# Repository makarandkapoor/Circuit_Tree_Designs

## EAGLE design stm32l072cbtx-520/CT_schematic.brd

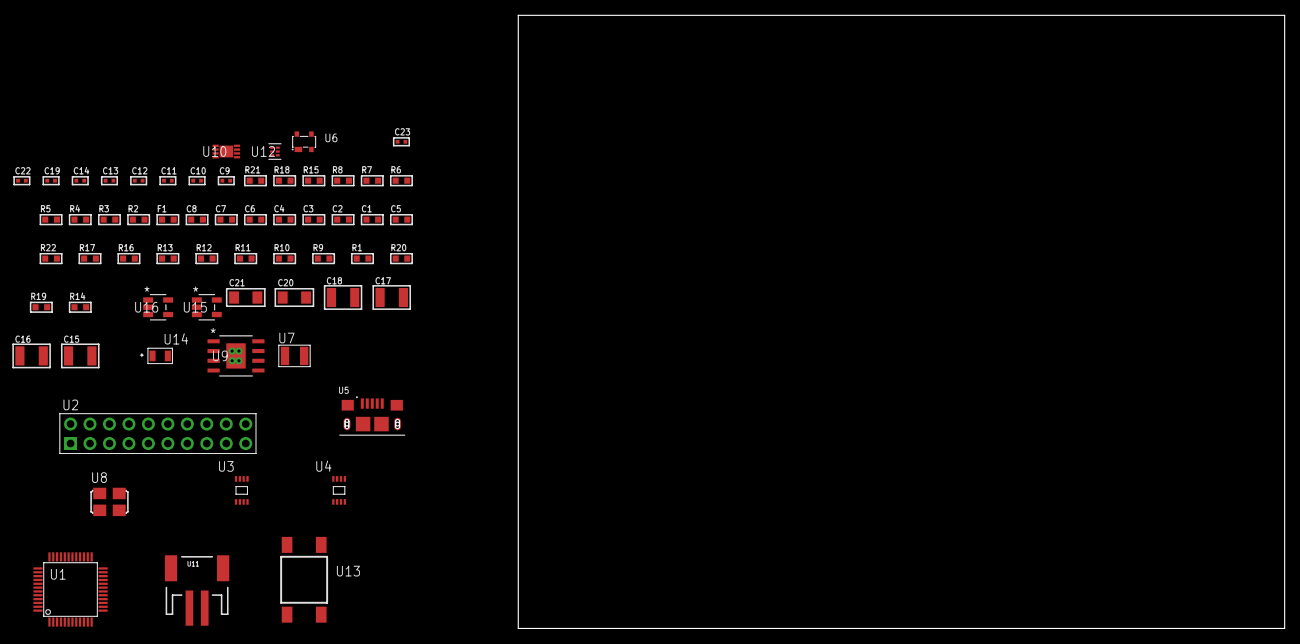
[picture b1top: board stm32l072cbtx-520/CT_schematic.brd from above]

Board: 2 copper layers, 122.6 x 80.0 mm, 62 parts (0 on the bottom side), 31 nets, no tracks yet.

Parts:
C1, C2, C3, C4, C8: 1e-07; C0603
C5: 4.7e-06; C0603
C6: 1e-08; C0603
C7: 1e-06; C0603
C9, C10: 1e-11; C0402
C11, C19: 1e-07; C0402
C12, C13, C14, C22, C23: 1e-08; C0402
C15, C16, C17, C18: 1e-05; C1210
C20, C21: 1e-05; C1206
F1: 240.0; L0603
R1, R9, R10, R11, R12, R13, R16, R17, R22: 10000.0; R0603
R2: 1000.0; R0603
R3: 1600.5; R0603
R4: 4700.0; R0603
R5, R6, R7, R8, R15: 2200.0; R0603
R14: 4031.5447154472; R0603
R18: 9100.0; R0603
R19: 680000.0; R0603
R20: 120000.0; R0603
R21: 2000.0; R0603
U1: STM32L072CBT6; LQFP48
U2: TST-110-05-T-D-RA
U3: 24AA16-I/MC; TDFN-8/6MM
U4: 24AA64T-I/MNY; TDFN-8/6MM
U5: 10118193-0001LF; FCI_10118193-0001LF
U6: prtr5v0u2ax; SOT143B
U7: ABS07-32.768KHZ-7-T
U8: ASFL1-25MHZ-NCS; ASFL1
U9: MIC5234YME; SOIC-8_EP
U10: MCP73831T-2ACI/MC; DFN8_2X3MC
U11: S2B-PH-SM4-TB(LF)(SN); JST-2-SMD
U12: TPS3895ADRYR; SON-6
U13: 4-1437565-2; SW_4-1437565-2
U14: Q65110A2395; LGM67K-G1J2-24-Z
U15, U16: nc7sz125m5x; NC7SZ125M5X

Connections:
CLK_CRYSTAL_U1_3: C9.1, U1.3, U7.1
CLK_CRYSTAL_U1_4: C10.1, U1.4, U7.2
CLK_U1_5: U1.5, U8.3
GND: C1.2, C2.2, C3.2, C4.2, C5.2, C6.2, C7.2, C8.2, C9.2, C10.2, C11.2, C12.2, C13.2, C14.2, C15.2, C16.2, C17.2, C18.2, C19.2, C20.2, C21.2, C22.2, C23.2, R2.2, R9.2, R11.2, R13.2, R15.2, R18.2, R20.2, R21.2, U1.8, U1.23, U1.35, U1.47, U2.4, U2.6, U2.8, U2.10, U2.12, U2.14, U2.16, U2.18, U2.20, U3.4, U3.7, U4.4, U4.7, U5.5, U5.6, U5.7, U5.8, U5.9, U6.1, U8.2, U9.7, U9.EPAD, U10.6, U10.9, U11.2, U12.2, U14.C, U15.2, U15.3, U16.1, U16.3
INPUT_USBPOWER_5V: C20.1, R22.2, U5.1, U6.4, U10.1, U10.2
NET_U1_7: R4.1, U1.7, U16.4
NET_U1_9: C6.1, C7.1, F1.1, U1.9
NET_U1_21: R7.1, U1.21, U3.6
NET_U1_22: R8.1, U1.22, U3.5
NET_U1_30: R5.1, U1.30, U4.6
NET_U1_31: R6.1, U1.31, U4.5
NET_U1_44: R9.1, U1.44
NET_U1_45: R3.1, U1.45, U14.A
NET_U1_46: R1.1, U1.46, U13.3, U13.4
NET_U4_1: R11.1, U4.1
NET_U4_2: R12.1, U4.2
NET_U4_3: R13.1, U4.3
NET_U9_4: R14.2, R15.1, U9.4
NET_U10_5: R22.1, U10.5
NET_U10_8: R21.1, U10.8
NET_U12_1: R17.1, R18.1, U12.1
NET_U12_3: R19.2, R20.1, U12.3
NET_U12_4: R16.1, U12.4, U15.4, U16.2
NET_U13_1: R2.1, U13.1, U13.2
PROC_SYS_SWCLK: U1.37, U2.9
PROC_SYS_SWDIO: U1.34, U2.7
PROC_USB_DM: U1.32, U5.2, U6.3
PROC_USB_DP: U1.33, U5.3, U6.2
RST_OUT_U2_SRESET_B: R10.1, U2.15, U15.1
VCC_S1_3V7: C15.1, C16.1, C21.1, U9.5, U9.8, U10.3, U10.4, U11.1
VCC_TIER1_3V3: C1.1, C2.1, C3.1, C4.1, C5.1, C8.1, C11.1, C12.1, C13.1, C14.1, C17.1, C18.1, C19.1, C22.1, C23.1, F1.2, R1.2, R3.2, R4.2, R5.2, R6.2, R7.2, R8.2, R10.2, R12.2, R14.1, R16.2, R17.2, R19.1, U1.1, U1.24, U1.36, U1.48, U2.1, U3.8, U4.8, U8.4, U9.1, U12.6, U15.5, U16.5

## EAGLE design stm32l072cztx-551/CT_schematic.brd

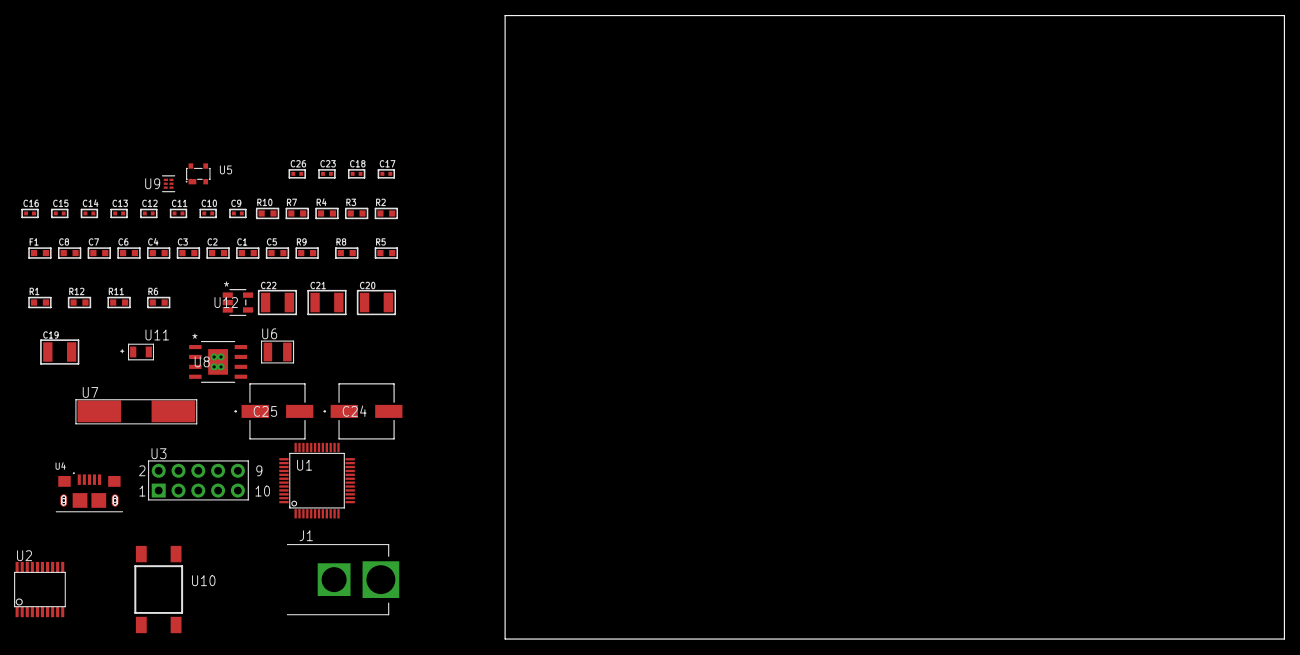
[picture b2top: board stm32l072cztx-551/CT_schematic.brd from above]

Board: 2 copper layers, 156.9 x 80.0 mm, 52 parts (0 on the bottom side), 34 nets, no tracks yet.

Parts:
C1, C2, C3, C4, C8: 1e-07; C0603
C5: 4.7e-06; C0603
C6: 1e-08; C0603
C7: 1e-06; C0603
C9, C10, C11, C12: 1e-11; C0402
C13, C14, C15, C16, C17, C18, C23: 1e-07; C0402
C19, C20, C21, C22: 1e-05; C1210
C24, C25: 0.0001; EXV-9H
C26: 1e-08; C0402
F1: 240.0; L0603
J1: PJ-037B; PJ-037B_PACKAGE
R1, R5, R8, R9: 10000.0; R0603
R2: 1000.0; R0603
R3: 1600.5; R0603
R4: 4700.0; R0603
R6: 4031.5447154472; R0603
R7: 2200.0; R0603
R10: 9100.0; R0603
R11: 680000.0; R0603
R12: 120000.0; R0603
U1: STM32L072CZT6; LQFP48
U2: SP3203ECY-L/TR; TSSOP20-I
U3: HTSS-105-01-G-D
U4: 10118193-0001LF; FCI_10118193-0001LF
U5: prtr5v0u2ax; SOT143B
U6: ABS07-32.768KHZ-7-T
U7: ABLS-25.000MHZ-B2F-T
U8: MIC5234YME; SOIC-8_EP
U9: TPS3895ADRYR; SON-6
U10: 4-1437565-2; SW_4-1437565-2
U11: Q65110A2395; LGM67K-G1J2-24-Z
U12: nc7sz125m5x; NC7SZ125M5X

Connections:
CLK_CRYSTAL_U1_3: C9.1, U1.3, U6.1
CLK_CRYSTAL_U1_4: C10.1, U1.4, U6.2
CLK_CRYSTAL_U1_5: C11.1, U1.5, U7.1
CLK_CRYSTAL_U1_6: C12.1, U1.6, U7.2
GND: C1.2, C2.2, C3.2, C4.2, C5.2, C6.2, C7.2, C8.2, C9.2, C10.2, C11.2, C12.2, C13.2, C14.2, C17.2, C18.2, C19.2, C20.2, C21.2, C22.2, C23.2, C24.2, C25.2, C26.2, J1.2, R2.2, R5.2, R7.2, R10.2, R12.2, U1.8, U1.23, U1.35, U1.47, U2.18, U3.9, U4.5, U4.6, U4.7, U4.8, U4.9, U5.1, U8.7, U8.EPAD, U9.2, U11.C, U12.1, U12.3
NET_U1_7: R4.1, U1.7, U12.4
NET_U1_9: C6.1, C7.1, F1.1, U1.9
NET_U1_44: R5.1, U1.44
NET_U1_45: R3.1, U1.45, U11.A
NET_U1_46: R1.1, U1.46, U10.3, U10.4
NET_U2_1: C15.1, U2.1
NET_U2_2: C17.1, U2.2
NET_U2_3: C15.2, U2.3
NET_U2_4: C16.1, U2.4
NET_U2_5: C16.2, U2.5
NET_U2_6: C18.1, U2.6
NET_U3_3: U2.14, U3.3
NET_U3_4: U2.13, U3.4
NET_U3_5: U2.17, U3.5
NET_U3_6: U2.16, U3.6
NET_U5_4: U4.1, U5.4
NET_U8_4: R6.2, R7.1, U8.4
NET_U9_1: R9.1, R10.1, U9.1
NET_U9_3: R11.2, R12.1, U9.3
NET_U9_4: R8.1, U9.4, U12.2
NET_U10_1: R2.1, U10.1, U10.2
PROC_LPUART1_CTS: U1.16, U2.8
PROC_LPUART1_RTS: U1.19, U2.10
PROC_LPUART1_RX: U1.13, U2.11
PROC_LPUART1_TX: U1.12, U2.7
PROC_USB_DM: U1.32, U4.2, U5.3
PROC_USB_DP: U1.33, U4.3, U5.2
VCC_S1_10V3: C19.1, C20.1, C24.1, C25.1, J1.1, U8.5, U8.8
VCC_TIER1_3V3: C1.1, C2.1, C3.1, C4.1, C5.1, C8.1, C13.1, C14.1, C21.1, C22.1, C23.1, C26.1, F1.2, R1.2, R3.2, R4.2, R6.1, R8.2, R9.2, R11.1, U1.1, U1.24, U1.36, U1.48, U2.12, U2.19, U8.1, U9.6, U12.5

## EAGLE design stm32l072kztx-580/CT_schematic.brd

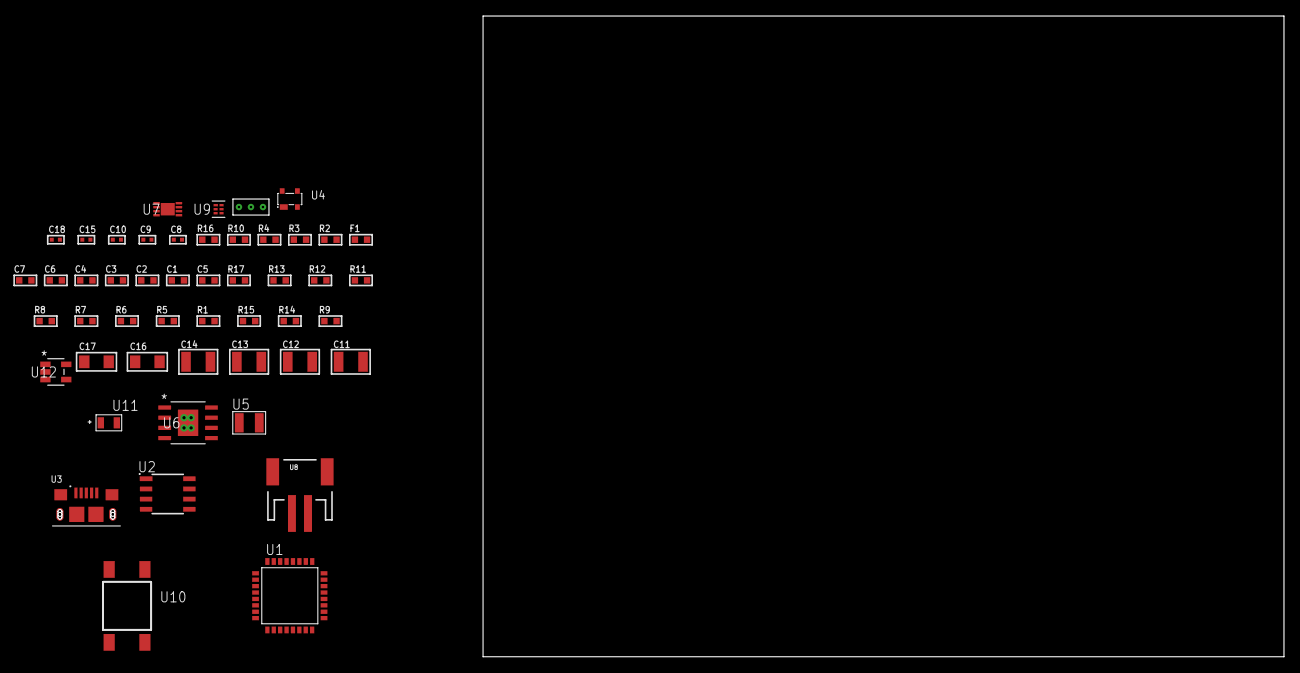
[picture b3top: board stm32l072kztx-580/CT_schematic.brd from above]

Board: 2 copper layers, 153.1 x 80.0 mm, 49 parts (0 on the bottom side), 28 nets, no tracks yet.

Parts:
C1, C2, C3, C4: 1e-07; C0603
C5: 4.7e-06; C0603
C6: 1e-08; C0603
C7: 1e-06; C0603
C8, C9: 1e-11; C0402
C10, C18: 1e-08; C0402
C11, C12, C13, C14: 1e-05; C1210
C15: 1e-07; C0402
C16, C17: 1e-05; C1206
F1: 240.0; L0603
R1, R5, R6, R7, R8, R11, R12, R17: 10000.0; R0603
R2: 1000.0; R0603
R3: 910.0; R0603
R4: 4700.0; R0603
R9: 1402.2764227642; R0603
R10: 2200.0; R0603
R13: 82000.0; R0603
R14: 300000.0; R0603
R15: 120000.0; R0603
R16: 2000.0; R0603
U1: STM32L072KZT6; LQFP32
U2: AT25256B-SSHL-T; SOIC-8
U3: 10118193-0001LF; FCI_10118193-0001LF
U4: prtr5v0u2ax; SOT143B
U5: ABS07-32.768KHZ-7-T
U6: MIC5234YME; SOIC-8_EP
U7: MCP73831T-2ACI/MC; DFN8_2X3MC
U8: S2B-PH-SM4-TB(LF)(SN); JST-2-SMD
U9: TPS3895ADRYR; SON-6
U10: 4-1437565-2; SW_4-1437565-2
U11: Q65110A2395; LGM67K-G1J2-24-Z
U12: nc7sz125m5x; NC7SZ125M5X
U13: Dummy; DUMMY_PACKAGE_101

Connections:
CLK_CRYSTAL_U1_2: C8.1, U1.2, U5.1
CLK_CRYSTAL_U1_3: C9.1, U1.3, U5.2
GND: C1.2, C2.2, C3.2, C4.2, C5.2, C6.2, C7.2, C8.2, C9.2, C10.2, C11.2, C12.2, C13.2, C14.2, C15.2, C16.2, C17.2, C18.2, R2.2, R5.2, R10.2, R13.2, R15.2, R16.2, U1.16, U1.32, U2.4, U3.5, U3.6, U3.7, U3.8, U3.9, U4.1, U6.7, U6.EPAD, U7.6, U7.9, U8.2, U9.2, U11.C, U12.1, U12.3, U13.1
INPUT_USBPOWER_5V: C16.1, R17.2, U3.1, U4.4, U7.1, U7.2
NET_U1_4: R4.1, U1.4, U12.4
NET_U1_5: C6.1, C7.1, F1.1, U1.5
NET_U1_29: R3.1, U1.29, U11.A
NET_U1_30: R1.1, U1.30, U10.3, U10.4
NET_U1_31: R5.1, U1.31
NET_U2_3: R6.1, U2.3
NET_U2_7: R8.1, U2.7
NET_U6_4: R9.2, R10.1, U6.4
NET_U7_5: R17.1, U7.5
NET_U7_8: R16.1, U7.8
NET_U9_1: R12.1, R13.1, U9.1
NET_U9_3: R14.2, R15.1, U9.3
NET_U9_4: R11.1, U9.4, U12.2
NET_U10_1: R2.1, U10.1, U10.2
PROC_PA0: U1.6, U13.2
PROC_PA1: U1.7, U13.3
PROC_SPI1_MISO: U1.12, U2.2
PROC_SPI1_MOSI: U1.13, U2.5
PROC_SPI1_NSS: R7.1, U1.10, U2.1
PROC_SPI1_SCK: U1.11, U2.6
PROC_USB_DM: U1.21, U3.2, U4.3
PROC_USB_DP: U1.22, U3.3, U4.2
VCC_S1_3V7: C11.1, C12.1, C17.1, U6.5, U6.8, U7.3, U7.4, U8.1
VCC_TIER1_1V8: C1.1, C2.1, C3.1, C4.1, C5.1, C10.1, C13.1, C14.1, C15.1, C18.1, F1.2, R1.2, R3.2, R4.2, R6.2, R7.2, R8.2, R9.1, R11.2, R12.2, R14.1, U1.1, U1.17, U2.8, U6.1, U9.6, U12.5

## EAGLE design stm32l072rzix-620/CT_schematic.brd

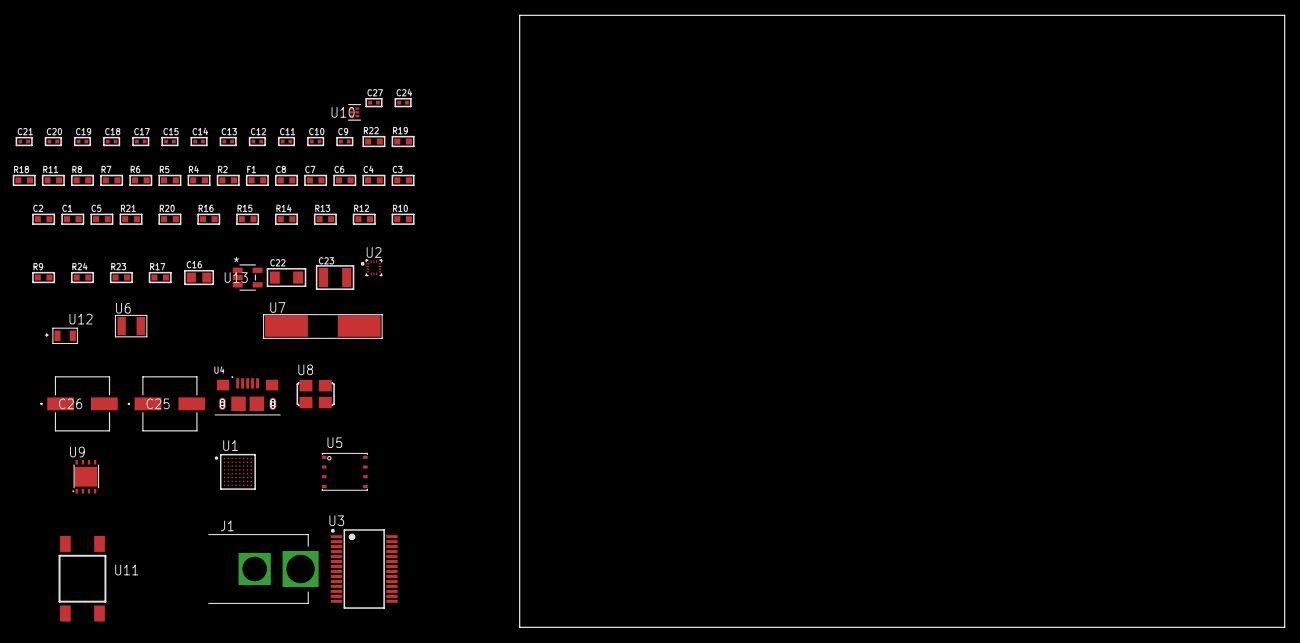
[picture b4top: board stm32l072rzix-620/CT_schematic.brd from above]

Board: 2 copper layers, 64 parts (0 on the bottom side), 36 nets, no tracks yet.

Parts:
C1, C2, C3, C4, C8: 1e-07; C0603
C5: 4.7e-06; C0603
C6: 1e-08; C0603
C7: 1e-06; C0603
C9, C10, C11, C12: 1e-11; C0402
C13, C14, C15, C17, C18, C24: 1e-07; C0402
C16: 4.7e-06; C0805
C19, C20, C21, C27: 1e-08; C0402
C22: 1e-05; C1206
C23: 1e-05; C1210
C25, C26: 0.0001; EXV-9H
F1: 240.0; L0603
J1: PJ-037B; PJ-037B_PACKAGE
R2, R19: 1000.0; R0603
R4, R11: 4700.0; R0603
R5, R6, R7, R8: 2200.0; R0603
R9, R10, R12, R13, R14, R15, R16, R20, R21: 10000.0; R0603
R17: 100000.0; R0603
R18: 2231.0; R0603
R22: 9100.0; R0603
R23: 680000.0; R0603
R24: 120000.0; R0603
U1: STM32L072RZI6; UFBGA64
U2: BMC150; LGA14R35P5X6_200X200X100
U3: FT232RL-REEL; SSOP-28
U4: 10118193-0001LF; FCI_10118193-0001LF
U5: 24AA256-I/MF; DFN8-S
U6: ABS07-32.768KHZ-7-T
U7: ABLS-25.000MHZ-B2F-T
U8: ASFL1-12MHZ-NCS; ASFL1
U9: LP3878SDX-ADJ/NOPB; WSON-8
U10: TPS3895ADRYR; SON-6
U11: 4-1437565-2; SW_4-1437565-2
U12: Q65110A2395; LGM67K-G1J2-24-Z
U13: nc7sz125m5x; NC7SZ125M5X

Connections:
CLK_CRYSTAL_U1_A1: C9.1, U1.A1, U6.1
CLK_CRYSTAL_U1_B1: C10.1, U1.B1, U6.2
CLK_CRYSTAL_U1_C1: C11.1, U1.C1, U7.1
CLK_CRYSTAL_U1_D1: C12.1, U1.D1, U7.2
CLK_U3_27: U3.27, U8.3
GND: C1.2, C2.2, C3.2, C4.2, C5.2, C6.2, C7.2, C8.2, C9.2, C10.2, C11.2, C12.2, C13.2, C14.2, C15.2, C16.2, C17.2, C18.2, C19.2, C20.2, C21.2, C22.2, C23.2, C24.2, C25.2, C26.2, C27.2, J1.2, R2.2, R9.2, R13.2, R14.2, R16.2, R19.2, R22.2, R24.2, U1.C2, U1.D4, U1.D5, U1.D6, U1.F1, U2.1, U2.6, U2.7, U2.9, U3.7, U3.18, U3.21, U3.25, U3.26, U4.5, U4.6, U4.7, U4.8, U4.9, U5.4, U8.2, U9.3, U9.PAD, U10.2, U12.C, U13.1, U13.3
NET_U1_A3: R6.1, U1.A3, U2.14
NET_U1_B3: R5.1, U1.B3, U2.11
NET_U1_B4: R9.1, U1.B4
NET_U1_E1: R4.1, U1.E1, U13.4
NET_U1_F8: R8.1, U1.F8, U5.5
NET_U1_G7: R7.1, U1.G7, U5.6
NET_U1_H1: C6.1, C7.1, F1.1, U1.G1, U1.H1
NET_U1_H8: U11.3, U11.4
NET_U3_14: R12.1, U3.14
NET_U3_17: C17.1, U3.17
NET_U3_19: R13.1, U3.19
NET_U4_1: R11.1, U4.1
NET_U4_2: U3.16, U4.2
NET_U4_3: U3.15, U4.3
NET_U5_1: R14.1, U5.1
NET_U5_2: R15.1, U5.2
NET_U5_3: R16.1, U5.3
NET_U9_1: C21.1, U9.1
NET_U9_6: R18.2, R19.1, U9.6
NET_U9_8: R17.1, U9.8
NET_U10_1: R21.1, R22.1, U10.1
NET_U10_3: R23.2, R24.1, U10.3
NET_U10_4: R20.1, U10.4, U13.2
NET_U11_1: R2.1, U11.1, U11.2
PROC_LPUART1_CTS: U1.G4, U3.3
PROC_LPUART1_RTS: U1.B5, U3.11
PROC_LPUART1_RX: U1.A8, U3.1
PROC_LPUART1_TX: U1.A7, U3.5
VCC_S1_11V0: C22.1, C25.1, C26.1, J1.1, R17.2, U9.4
VCC_TIER1_3V3: C1.1, C2.1, C3.1, C4.1, C5.1, C8.1, C13.1, C14.1, C15.1, C16.1, C18.1, C19.1, C20.1, C23.1, C24.1, C27.1, F1.2, R4.2, R5.2, R6.2, R7.2, R8.2, R10.1, R10.2, R12.2, R15.2, R18.1, R20.2, R21.2, R23.1, U1.B2, U1.D2, U1.E4, U1.E5, U1.E6, U2.8, U2.10, U2.12, U2.13, U3.4, U3.20, U5.7, U5.8, U8.4, U9.5, U10.6, U13.5

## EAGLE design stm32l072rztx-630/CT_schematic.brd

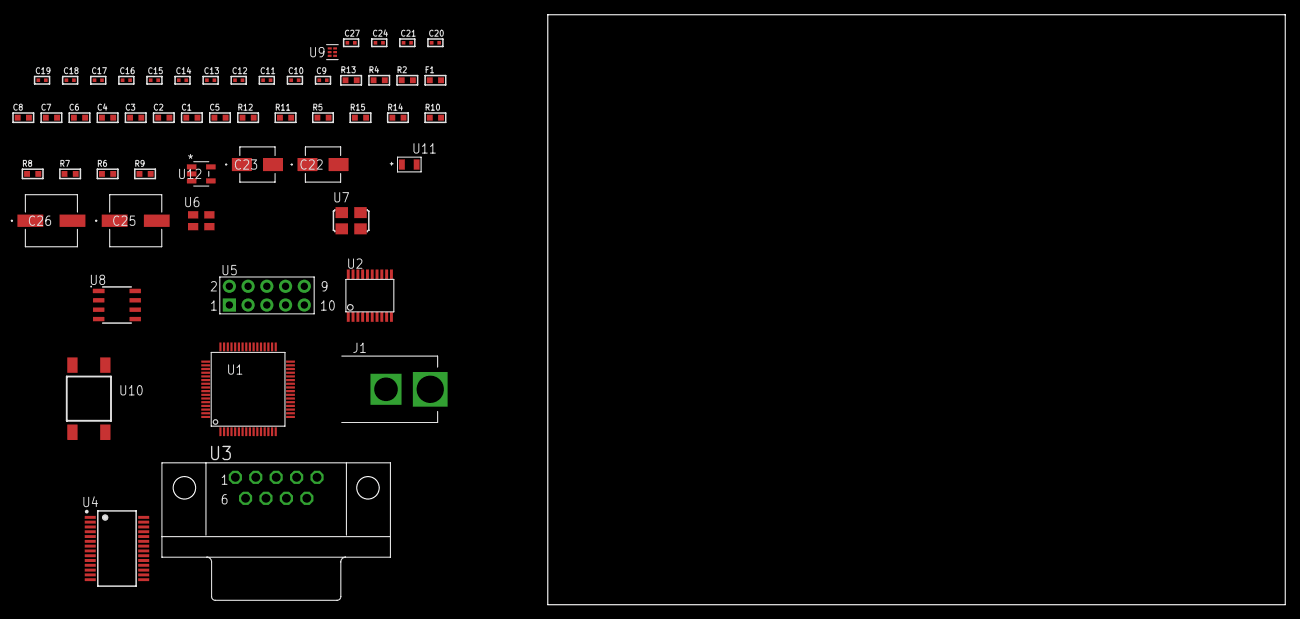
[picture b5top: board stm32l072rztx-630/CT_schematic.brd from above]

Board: 2 copper layers, 100.0 x 80.0 mm, 54 parts (0 on the bottom side), 45 nets, no tracks yet.

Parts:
C1, C2, C3, C4, C8: 1e-07; C0603
C5: 4.7e-06; C0603
C6: 1e-08; C0603
C7: 1e-06; C0603
C9, C10, C11, C12, C13, C14, C15, C16, C17, C18, C19, C24: 1e-07; C0402
C20, C21, C27: 1e-08; C0402
C22: 1e-06; EXV-9B
C23: 2.2e-06; EXV-9B
C25, C26: 0.0001; EXV-9H
F1: 240.0; L0603
J1: PJ-037B; PJ-037B_PACKAGE
R2: 1000.0; R0603
R4: 4700.0; R0603
R5, R11, R12: 10000.0; R0603
R6, R7, R8, R10: 100000.0; R0603
R9: 164658.62; R0603
R13: 9100.0; R0603
R14: 680000.0; R0603
R15: 120000.0; R0603
U1: STM32L072RZT6; LQFP64
U2: SP3203ECY-L/TR; TSSOP20-I
U3: 182-009-113R531; 182-009-MALE
U4: ST3241EBPR; SSOP-28
U5: HTSS-105-01-G-D
U6: ASEK-32.768KHz-ECST; ASEK
U7: ASFL1-25MHZ-NCS; ASFL1
U8: LP2954AIMX/NOPB; LP2954
U9: TPS3895ADRYR; SON-6
U10: 4-1437565-2; SW_4-1437565-2
U11: Q65110A2395; LGM67K-G1J2-24-Z
U12: nc7sz125m5x; NC7SZ125M5X

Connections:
CLK_U1_3: U1.3, U6.3
CLK_U1_5: U1.5, U7.3
GND: C1.2, C2.2, C3.2, C4.2, C5.2, C6.2, C7.2, C8.2, C9.2, C10.2, C13.2, C14.2, C15.2, C18.2, C19.2, C20.2, C21.2, C22.2, C23.2, C24.2, C25.2, C26.2, C27.2, J1.2, R2.2, R5.2, R10.2, R13.2, R15.2, U1.12, U1.18, U1.31, U1.47, U1.63, U2.18, U3.5, U4.23, U4.25, U5.9, U6.2, U7.2, U8.4, U9.2, U11.C, U12.1, U12.3
NET_U1_7: R4.1, U1.7, U12.4
NET_U1_13: C6.1, C7.1, F1.1, U1.13
NET_U1_60: R5.1, U1.60
NET_U1_62: U10.3, U10.4
NET_U2_1: C11.1, U2.1
NET_U2_2: C13.1, U2.2
NET_U2_3: C11.2, U2.3
NET_U2_4: C12.1, U2.4
NET_U2_5: C12.2, U2.5
NET_U2_6: C14.1, U2.6
NET_U3_2: U2.14, U3.2
NET_U3_3: U2.17, U3.3
NET_U3_7: U2.13, U3.7
NET_U3_8: U2.16, U3.8
NET_U4_1: C17.1, U4.1
NET_U4_2: C17.2, U4.2
NET_U4_3: C19.1, U4.3
NET_U4_22: R6.1, U4.22
NET_U4_24: C16.2, U4.24
NET_U4_27: C18.1, U4.27
NET_U4_28: C16.1, U4.28
NET_U5_3: U4.4, U5.3
NET_U5_4: U4.5, U5.4
NET_U5_5: U4.9, U5.5
NET_U5_6: U4.10, U5.6
NET_U8_3: R8.1, U8.3
NET_U8_5: R7.1, U8.5
NET_U8_7: R9.2, R10.1, U8.7
NET_U9_1: R12.1, R13.1, U9.1
NET_U9_3: R14.2, R15.1, U9.3
NET_U9_4: R11.1, U9.4, U12.2
NET_U10_1: R2.1, U10.1, U10.2
PROC_LPUART1_CTS: U1.22, U2.8
PROC_LPUART1_RTS: U1.27, U2.10
PROC_LPUART1_RX: U1.8, U2.11
PROC_LPUART1_TX: U1.9, U2.7
PROC_USART1_CTS: U1.44, U4.13
PROC_USART1_RTS: U1.45, U4.18
PROC_USART1_RX: U1.43, U4.19
PROC_USART1_TX: U1.42, U4.14
VCC_S1_6V2: C22.1, C25.1, C26.1, J1.1, R8.2, U8.8
VCC_TIER1_3V3: C1.1, C2.1, C3.1, C4.1, C5.1, C8.1, C9.1, C10.1, C15.1, C20.1, C21.1, C23.1, C24.1, C27.1, F1.2, R4.2, R6.2, R7.2, R9.1, R11.2, R12.2, R14.1, U1.1, U1.19, U1.32, U1.48, U1.64, U2.12, U2.19, U4.26, U6.4, U7.4, U8.1, U9.6, U12.5

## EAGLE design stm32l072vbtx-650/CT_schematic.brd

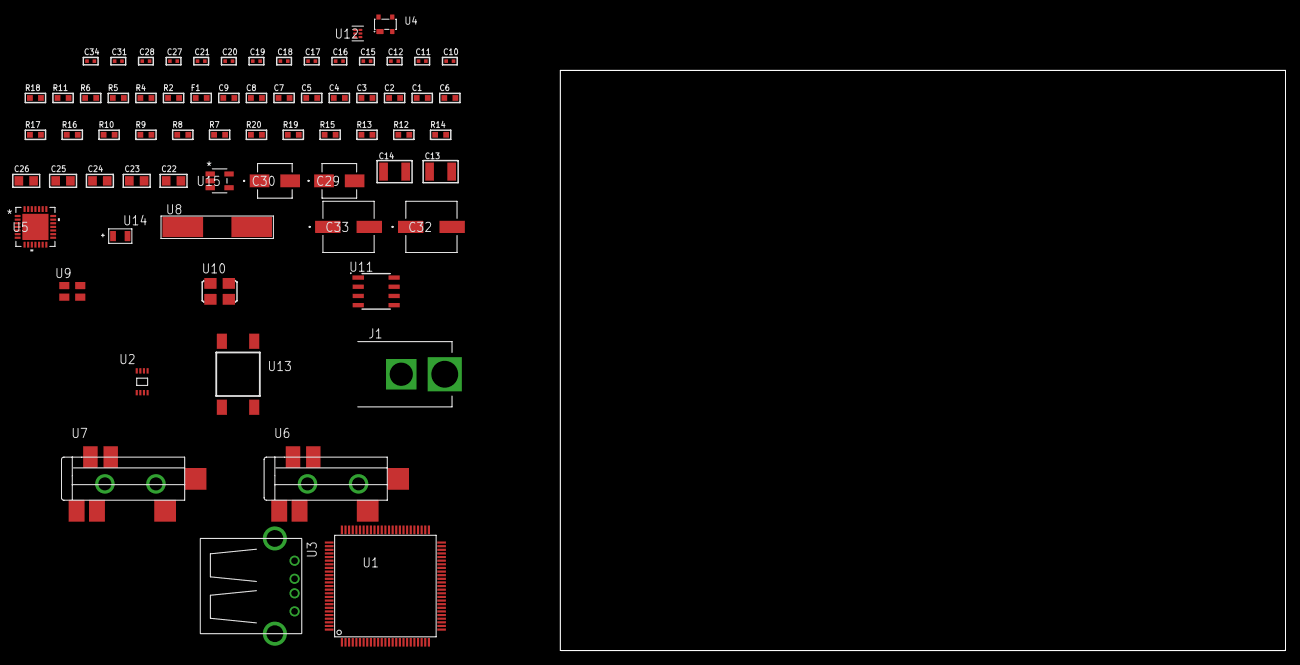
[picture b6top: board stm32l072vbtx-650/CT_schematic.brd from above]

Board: 2 copper layers, 100.0 x 80.0 mm, 69 parts (0 on the bottom side), 30 nets, no tracks yet.

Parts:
C1, C2, C3, C4, C5, C9: 1e-07; C0603
C6: 4.7e-06; C0603
C7: 1e-08; C0603
C8: 1e-06; C0603
C10, C11: 1e-11; C0402
C12, C27, C28, C34: 1e-08; C0402
C13, C14: 2.2e-05; C1210
C15, C16: 1e-09; C0402
C17, C18, C19, C20, C21, C31: 1e-07; C0402
C22, C23, C24, C25, C26: 1e-05; C0805
C29: 1e-06; EXV-9B
C30: 2.2e-06; EXV-9B
C32, C33: 0.0001; EXV-9H
F1: 240.0; L0603
J1: PJ-037B; PJ-037B_PACKAGE
R2: 1000.0; R0603
R4: 4700.0; R0603
R5, R6: 2200.0; R0603
R7, R16, R17: 10000.0; R0603
R8, R9, R10: 47000.0; R0603
R11: 680.0; R0603
R12, R13, R15: 100000.0; R0603
R14: 164658.62; R0603
R18: 9100.0; R0603
R19: 680000.0; R0603
R20: 120000.0; R0603
U1: STM32L072VBT6; LQFP100
U2: 24AA16-I/MC; TDFN-8/6MM
U3: 61400416021; USB-A-H
U4: prtr5v0u2ax; SOT143B
U5: WM8731CLSEFL; QFN-28
U6, U7: SJ-43515TS-SMT-TR
U8: ABLS-25.000MHZ-B2F-T
U9: ASEK-32.768KHz-ECST; ASEK
U10: ASFL1-12.288MHZ-EC-T; ASFL1
U11: LP2954AIMX/NOPB; LP2954
U12: TPS3895ADRYR; SON-6
U13: 4-1437565-2; SW_4-1437565-2
U14: Q65110A2395; LGM67K-G1J2-24-Z
U15: nc7sz125m5x; NC7SZ125M5X

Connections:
CLK_CRYSTAL_U1_12: C10.1, U1.12, U8.1
CLK_CRYSTAL_U1_13: C11.1, U1.13, U8.2
CLK_U1_8: U1.8, U9.3
CLK_U5_1: U5.1, U10.3
GND: C1.2, C2.2, C3.2, C4.2, C5.2, C6.2, C7.2, C8.2, C9.2, C10.2, C11.2, C12.2, C16.2, C17.2, C18.2, C19.2, C20.2, C21.2, C22.2, C23.2, C24.2, C25.2, C26.2, C27.2, C28.2, C29.2, C30.2, C31.2, C32.2, C33.2, C34.2, J1.2, R2.2, R7.2, R8.2, R9.2, R10.2, R15.2, R18.2, R20.2, U1.19, U1.20, U1.27, U1.49, U1.74, U1.99, U2.4, U3.4, U3.5, U3.6, U4.1, U5.4, U5.15, U5.19, U5.25, U5.26, U5.29, U6.1, U7.1, U9.2, U10.2, U11.4, U12.2, U14.C, U15.1, U15.3
NET_U1_14: R4.1, U1.14, U15.4
NET_U1_22: C7.1, C8.1, F1.1, U1.21, U1.22
NET_U1_68: R5.1, U1.68, U2.6
NET_U1_69: R6.1, U1.69, U2.5
NET_U1_94: R7.1, U1.94
NET_U1_98: U13.3, U13.4
NET_U4_4: U3.1, U4.4
NET_U5_20: C21.1, C26.1, U5.20
NET_U6_2: C14.1, R9.1, U6.2
NET_U6_5: C13.1, R8.1, U6.5
NET_U7_5: C15.1, C16.1, R10.1, R11.1, U7.5
NET_U11_3: R13.1, U11.3
NET_U11_5: R12.1, U11.5
NET_U11_7: R14.2, R15.1, U11.7
NET_U12_1: R17.1, R18.1, U12.1
NET_U12_3: R19.2, R20.1, U12.3
NET_U12_4: R16.1, U12.4, U15.2
NET_U13_1: R2.1, U13.1, U13.2
PROC_I2S2_CK: U1.52, U5.7
PROC_I2S2_SD: U1.18, U5.8
PROC_I2S2_WS: U1.51, U5.9, U5.11
PROC_USB_DM: U1.70, U3.2, U4.3
PROC_USB_DP: U1.71, U3.3, U4.2
VCC_S1_11V5: C29.1, C32.1, C33.1, J1.1, R13.2, U11.8
VCC_TIER1_3V3: C1.1, C2.1, C3.1, C4.1, C5.1, C6.1, C9.1, C12.1, C17.1, C18.1, C19.1, C20.1, C22.1, C23.1, C24.1, C25.1, C27.1, C28.1, C30.1, C31.1, C34.1, F1.2, R4.2, R5.2, R6.2, R12.2, R14.1, R16.2, R17.2, R19.1, U1.6, U1.28, U1.50, U1.73, U1.75, U1.100, U2.7, U2.8, U5.3, U5.5, U5.12, U5.18, U9.4, U10.4, U11.1, U12.6, U15.5

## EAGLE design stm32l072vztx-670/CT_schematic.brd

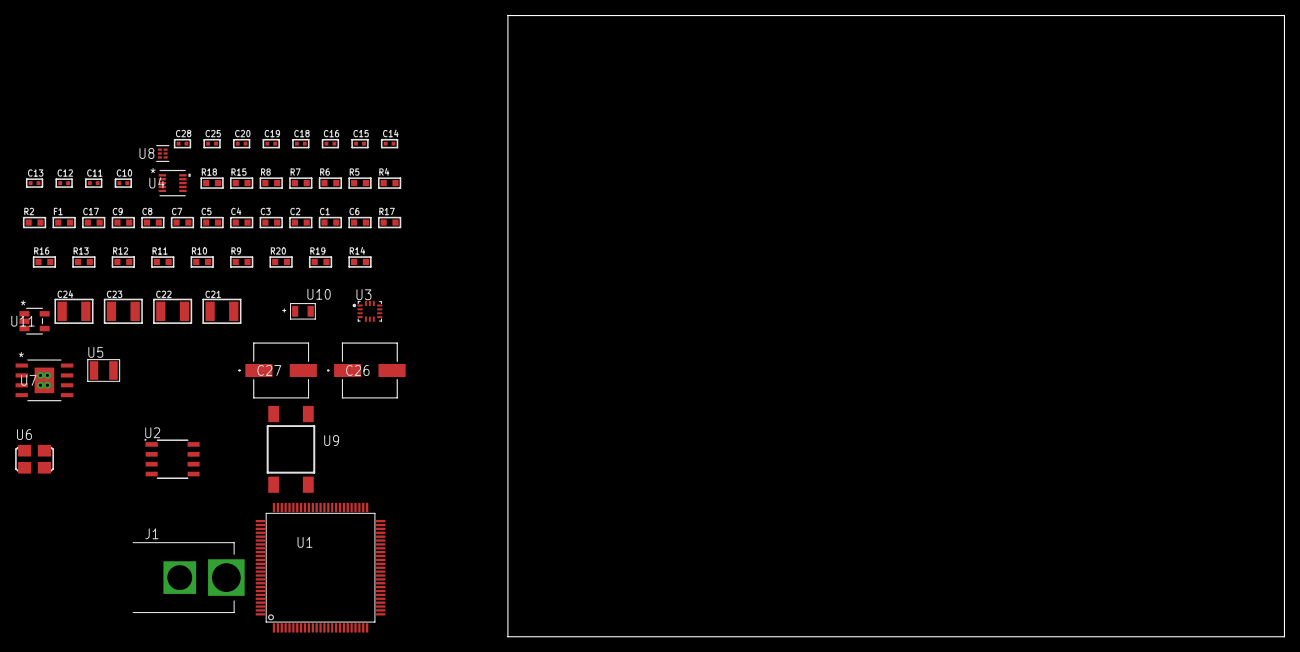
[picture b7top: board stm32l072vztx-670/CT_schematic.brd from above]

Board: 2 copper layers, 100.0 x 80.0 mm, 59 parts (0 on the bottom side), 26 nets, no tracks yet.

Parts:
C1, C2, C3, C4, C5, C9: 1e-07; C0603
C6: 4.7e-06; C0603
C7: 1e-08; C0603
C8, C17: 1e-06; C0603
C10, C11: 1e-11; C0402
C12, C20, C28: 1e-08; C0402
C13, C14, C15, C16, C18, C19, C25: 1e-07; C0402
C21, C22, C23, C24: 1e-05; C1210
C26, C27: 0.0001; EXV-9H
F1: 240.0; L0603
J1: PJ-037B; PJ-037B_PACKAGE
R2: 1000.0; R0603
R4: 4700.0; R0603
R5, R6, R7, R8, R15: 2200.0; R0603
R9, R10, R11, R12, R13, R16, R17: 10000.0; R0603
R14: 4031.5447154472; R0603
R18: 9100.0; R0603
R19: 680000.0; R0603
R20: 120000.0; R0603
U1: STM32L072VZT6; LQFP100
U2: AT25M02-SSHD-T; SOIC-8
U3: BMG250; LGA-14
U4: MAG3110FCR1; DFN-10
U5: ABS07-32.768KHZ-7-T
U6: ASFL1-25MHZ-NCS; ASFL1
U7: MIC5234YME; SOIC-8_EP
U8: TPS3895ADRYR; SON-6
U9: 4-1437565-2; SW_4-1437565-2
U10: Q65110A2395; LGM67K-G1J2-24-Z
U11: nc7sz125m5x; NC7SZ125M5X

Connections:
CLK_CRYSTAL_U1_8: C10.1, U1.8, U5.1
CLK_CRYSTAL_U1_9: C11.1, U1.9, U5.2
CLK_U1_12: U1.12, U6.3
GND: C1.2, C2.2, C3.2, C4.2, C5.2, C6.2, C7.2, C8.2, C9.2, C10.2, C11.2, C12.2, C13.2, C14.2, C15.2, C16.2, C17.2, C18.2, C19.2, C20.2, C21.2, C22.2, C23.2, C24.2, C25.2, C26.2, C27.2, C28.2, J1.2, R2.2, R9.2, R15.2, R18.2, R20.2, U1.19, U1.20, U1.27, U1.49, U1.74, U1.99, U2.4, U3.1, U3.6, U3.7, U4.5, U4.10, U6.2, U7.7, U7.EPAD, U8.2, U10.C, U11.1, U11.3
NET_U1_14: R4.1, U1.14, U11.4
NET_U1_22: C7.1, C8.1, F1.1, U1.21, U1.22
NET_U1_47: R7.1, U1.47, U3.13
NET_U1_48: R8.1, U1.48, U3.14
NET_U1_68: R5.1, U1.68, U4.7
NET_U1_69: R6.1, U1.69, U4.6
NET_U1_94: R9.1, U1.94
NET_U1_98: U9.3, U9.4
NET_U2_3: R10.1, U2.3
NET_U2_7: R12.1, U2.7
NET_U3_12: R13.1, U3.12
NET_U4_1: C15.1, U4.1
NET_U4_4: C18.1, U4.4
NET_U7_4: R14.2, R15.1, U7.4
NET_U8_1: R17.1, R18.1, U8.1
NET_U8_3: R19.2, R20.1, U8.3
NET_U8_4: R16.1, U8.4, U11.2
NET_U9_1: R2.1, U9.1, U9.2
PROC_GPIO_TO_U3_INT1: U1.1, U3.4
PROC_SPI1_NSS: R11.1, U2.1
VCC_S1_7V3: C21.1, C22.1, C26.1, C27.1, J1.1, U7.5, U7.8
VCC_TIER1_3V3: C1.1, C2.1, C3.1, C4.1, C5.1, C6.1, C9.1, C12.1, C13.1, C14.1, C16.1, C17.1, C19.1, C20.1, C23.1, C24.1, C25.1, C28.1, F1.2, R4.2, R5.2, R6.2, R7.2, R8.2, R10.2, R11.2, R12.2, R13.2, R14.1, R16.2, R17.2, R19.1, U1.6, U1.28, U1.50, U1.73, U1.75, U1.100, U2.8, U3.5, U3.8, U4.2, U4.8, U6.4, U7.1, U8.6, U11.5

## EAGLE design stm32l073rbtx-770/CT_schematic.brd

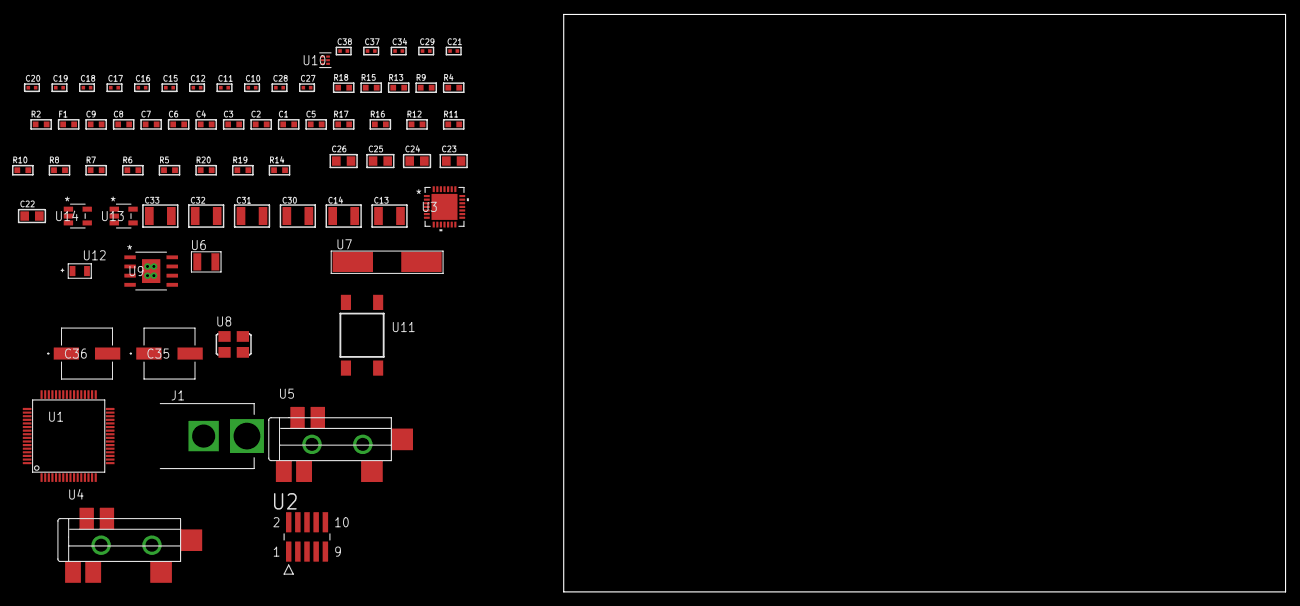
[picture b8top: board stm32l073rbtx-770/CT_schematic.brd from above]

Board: 2 copper layers, 100.0 x 80.0 mm, 72 parts (0 on the bottom side), 29 nets, no tracks yet.

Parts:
C1, C2, C3, C4, C6, C9: 1e-07; C0603
C5: 4.7e-06; C0603
C7: 1e-08; C0603
C8: 1e-06; C0603
C10, C11: 1e-11; C0402
C12, C17, C18, C19, C20, C21, C34: 1e-07; C0402
C13, C14: 2.2e-05; C1210
C15, C16: 1e-09; C0402
C22, C23, C24, C25, C26: 1e-05; C0805
C27, C28: 2.2e-11; C0402
C29, C37, C38: 1e-08; C0402
C30, C31, C32, C33: 1e-05; C1210
C35, C36: 0.0001; EXV-9H
F1: 240.0; L0603
J1: PJ-037B; PJ-037B_PACKAGE
R2: 1000.0; R0603
R4: 4700.0; R0603
R5, R6, R7, R8, R16, R17: 10000.0; R0603
R9: 5.0; R0603
R10, R11, R12: 47000.0; R0603
R13: 680.0; R0603
R14: 4031.5447154472; R0603
R15: 2200.0; R0603
R18: 9100.0; R0603
R19: 680000.0; R0603
R20: 120000.0; R0603
U1: STM32L073RBT6; LQFP64
U2: FTSH-105-01-L-DV-K; SAMTEC_FTSH-105-01-L-DV-K
U3: WM8731CLSEFL; QFN-28
U4, U5: SJ-43515TS-SMT-TR
U6: ABS07-32.768KHZ-7-T
U7: ABLS-12.288MHZ-B4-T
U8: ASFL1-25MHZ-NCS; ASFL1
U9: MIC5234YME; SOIC-8_EP
U10: TPS3895ADRYR; SON-6
U11: 4-1437565-2; SW_4-1437565-2
U12: Q65110A2395; LGM67K-G1J2-24-Z
U13, U14: nc7sz125m5x; NC7SZ125M5X

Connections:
CLK_CRYSTAL_U1_3: C10.1, U1.3, U6.1
CLK_CRYSTAL_U1_4: C11.1, U1.4, U6.2
CLK_CRYSTAL_U3_1: C27.1, U3.1, U7.1
CLK_CRYSTAL_U3_2: C28.1, U3.2, U7.2
CLK_U1_5: U1.5, U8.3
GND: C1.2, C2.2, C3.2, C4.2, C5.2, C6.2, C7.2, C8.2, C9.2, C10.2, C11.2, C12.2, C16.2, C17.2, C18.2, C19.2, C20.2, C21.2, C22.2, C23.2, C24.2, C25.2, C26.2, C27.2, C28.2, C29.2, C30.2, C31.2, C32.2, C33.2, C34.2, C35.2, C36.2, C37.2, C38.2, J1.2, R2.2, R5.2, R9.2, R10.2, R11.2, R12.2, R15.2, R18.2, R20.2, U1.12, U1.18, U1.31, U1.47, U1.63, U2.3, U2.5, U3.4, U3.15, U3.19, U3.25, U3.26, U3.29, U4.1, U5.1, U8.2, U9.7, U9.EPAD, U10.2, U12.C, U13.2, U13.3, U14.1, U14.3
NET_U1_1: C6.1, U1.1
NET_U1_7: R4.1, U1.7, U14.4
NET_U1_13: C7.1, C8.1, F1.1, U1.13
NET_U1_60: R5.1, U1.60
NET_U1_62: U11.3, U11.4
NET_U2_9: R9.1, U2.9
NET_U3_20: C21.1, C26.1, U3.20
NET_U4_2: C14.1, R11.1, U4.2
NET_U4_5: C13.1, R10.1, U4.5
NET_U5_5: C15.1, C16.1, R12.1, R13.1, U5.5
NET_U9_4: R14.2, R15.1, U9.4
NET_U10_1: R17.1, R18.1, U10.1
NET_U10_3: R19.2, R20.1, U10.3
NET_U10_4: R16.1, U10.4, U13.4, U14.2
NET_U11_1: R2.1, U11.1, U11.2
PROC_I2S2_CK: U1.34, U3.7
PROC_I2S2_SD: U1.11, U3.8
PROC_I2S2_WS: U1.33, U3.9, U3.11
PROC_SYS_SWCLK: R7.1, U1.49, U2.4
PROC_SYS_SWDIO: R8.1, U1.46, U2.2
RST_OUT_U2_JTAG_RST_B: R6.1, U2.10, U13.1
VCC_S1_8V8: C30.1, C31.1, C35.1, C36.1, J1.1, U9.5, U9.8
VCC_TIER1_3V3: C1.1, C2.1, C3.1, C4.1, C5.1, C9.1, C12.1, C17.1, C18.1, C19.1, C20.1, C22.1, C23.1, C24.1, C25.1, C29.1, C32.1, C33.1, C34.1, C37.1, C38.1, F1.2, R4.2, R6.2, R7.2, R8.2, R14.1, R16.2, R17.2, R19.1, U1.19, U1.32, U1.48, U1.64, U2.1, U3.3, U3.5, U3.12, U3.18, U8.4, U9.1, U10.6, U13.5, U14.5
